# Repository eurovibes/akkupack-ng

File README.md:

<!-- SPDX-FileCopyrightText: 2024 Benedikt Spranger <b.spranger@linutronix.de> -->
<!-- SPDX-License-Identifier: CERN-OHL-S-2.0 -->

# Akkupack-NG - A AKKU-Pack gas gauge

## License rules

akkupack-ng is provided under the terms of the CERN-OHL-S license
version 2 as provided in the LICENSES/CERN-OHL-S-2.0 file.

Instead of adding license boilerplates to the individual files,
akkupack-ng uses SPDX license identifiers, which are machine parseable
and considered legaly equivalent.

The SPDX license identifier in akkupack-ng shall be added at the first
possible line in a file which can contain a comment. This is normally the
first line except for scripts. Scripts require the #!PATH_TO_INTERPRETER tag
in the first line; place the SPDX identifier into the second line.

The SPDX license identifier is added in form of a comment.

## Copyright and License

> Copyright Benedikt Spranger 2024.
> This source describes Open Hardware and is licensed under the CERNOHL-S v2.
> You may redistribute and modify this source and make products using it
> under the terms of the CERN-OHL-S v2 (https://ohwr.org/cern ohl s v2.txt ).
> This source is distributed WITHOUT ANY EXPRESS OR IMPLIED WARRANTY, INCLUDING
> OF MERCHANTABILITY, SATISFACTORY QUALITY AND FITNESS FOR A PARTICULAR PURPOSE.
> Please see the CERN-OHL-S v2 for applicable conditions.
> Source location: https://github.com/eurovibes/akkupack-ng
> As per CERN-OHL-S v2 section 4, should You produce hardware based
> on this source, You must where practicable maintain the Source Location
> visible on the external case of the akkupack-ng or other products you
> make using this source.

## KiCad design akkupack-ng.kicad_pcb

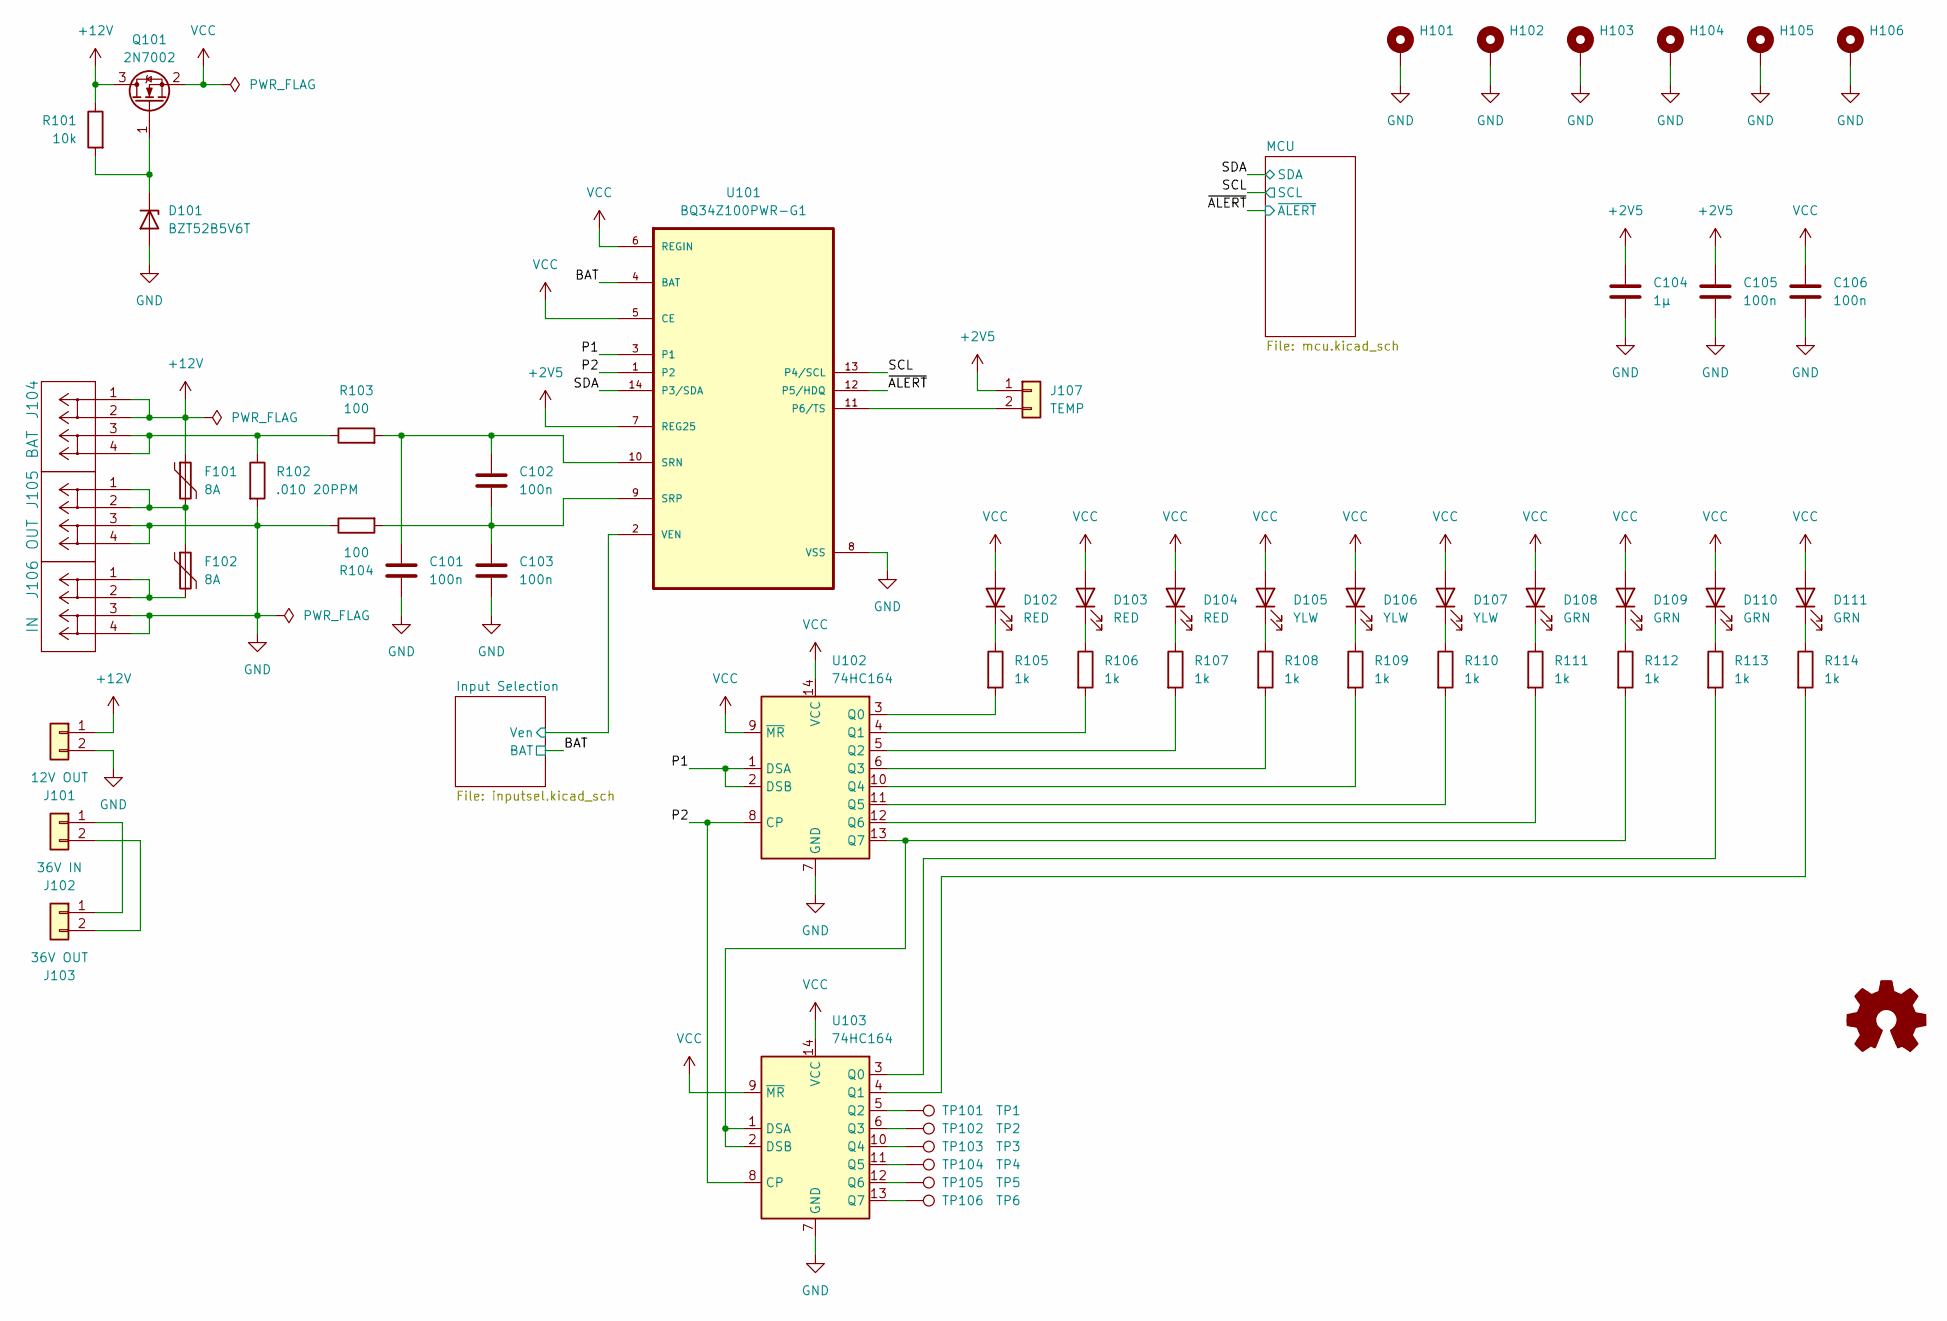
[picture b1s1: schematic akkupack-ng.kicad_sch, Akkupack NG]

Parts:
C101, C102, C103, C105, C106: 100n; C_0402_1005Metric; lcsc# C307331
C104: 1µ; C_0402_1005Metric; lcsc# C52923
D101: BZT52B5V6T; D_SOD-123F; lcsc# C22399881
D102, D103, D104: RED; LED_0603_1608Metric; lcsc# C2286
D105, D106, D107: YLW; LED_0603_1608Metric; lcsc# C965803
D108, D109, D110, D111: GRN; LED_0603_1608Metric; lcsc# C965804
F101, F102: 8A; PTR016V0800; digikey# PTR016V0800-BK-ND
H101, H102, H103, H104, H105, H106: MountingHole_3.2mm_M3_Pad
J101: 12V OUT; TerminalBlock_WAGO_236-402_1x02_P5.00mm_45Degree; digikey# 2946-236-402-ND
J102: 36V IN; TerminalBlock_WAGO_236-402_1x02_P5.00mm_45Degree; digikey# 2946-236-402-ND
J103: 36V OUT; TerminalBlock_WAGO_236-402_1x02_P5.00mm_45Degree; digikey# 2946-236-402-ND
J104: BAT; 745-302_WAGO; digikey# 2946-745-302-ND
J105: OUT; 745-302_WAGO; digikey# 2946-745-302-ND
J106: IN; 745-302_WAGO; digikey# 2946-745-302-ND
J107: TEMP; TerminalBlock_WAGO_236-402_1x02_P5.00mm_45Degree; digikey# 2946-236-402-ND
Q101: 2N7002; SOT-23; lcsc# C8545
R101: 10k; R_0402_1005Metric; lcsc# C25744
R102: .010 20PPM; R_2512_6332Metric; lcsc# C466594
R103, R104: 100; R_0402_1005Metric; lcsc# C25076
R105, R106, R107, R108, R109, R110, R111, R112, R113, R114: 1k; R_0402_1005Metric; lcsc# C11702
TP101: TP1; TestPoint_Pad_D1.0mm
TP102: TP2; TestPoint_Pad_D1.0mm
TP103: TP3; TestPoint_Pad_D1.0mm
TP104: TP4; TestPoint_Pad_D1.0mm
TP105: TP5; TestPoint_Pad_D1.0mm
TP106: TP6; TestPoint_Pad_D1.0mm
U101: BQ34Z100PWR-G1; SOP65P640X120-14N; lcsc# C91302
U102, U103: 74HC164; TSSOP-14_4.4x5mm_P0.65mm; lcsc# C406867

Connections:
+2V5: C104.1, C105.1, J107.1, U101.7 (REG25); also elsewhere on the board
+12V: F101.1, J101.1, J104.1, J104.2, Q101.3 (D), R101.1; also elsewhere on the board
/BAT: U101.4 (BAT); also elsewhere on the board
/Input Selection/Ven: U101.2 (VEN); also elsewhere on the board
/P1: U101.3 (P1), U102.1 (DSA), U102.2 (DSB)
/P2: U101.1 (P2), U102.8 (CP), U103.8 (CP)
/SCL: U101.13 (P4/SCL); also elsewhere on the board
/SDA: U101.14 (P3/SDA); also elsewhere on the board
/~ALERT: U101.12 (P5/HDQ); also elsewhere on the board
GND: C101.2, C103.2, C104.2, C105.2, C106.2, D101.2 (A), H101.1, H102.1, H103.1, H104.1, H105.1, H106.1, J101.2, J105.3, J105.4, J106.3, J106.4, R102.2, R104.1, U101.8 (VSS), U102.7 (GND), U103.7 (GND); also elsewhere on the board
unnamed: D101.1 (K), Q101.1 (G), R101.2
unnamed: D102.1 (K), R105.1
unnamed: D103.1 (K), R106.1
unnamed: D104.1 (K), R107.1
unnamed: D105.1 (K), R108.1
unnamed: D106.1 (K), R109.1
unnamed: D107.1 (K), R110.1
unnamed: D108.1 (K), R111.1
unnamed: D109.1 (K), R112.1
unnamed: D110.1 (K), R113.1
unnamed: D111.1 (K), R114.1
unnamed: F101.2, F102.1, J105.1, J105.2
unnamed: F102.2, J106.1, J106.2
unnamed: J102.1, J103.1
unnamed: J102.2, J103.2
unnamed: J104.3, J104.4, R102.1, R103.1
unnamed: J107.2, U101.11 (P6/TS)
unnamed: C101.1, C102.1, R103.2, U101.10 (SRN)
unnamed: C102.2, C103.1, R104.2, U101.9 (SRP)
unnamed: R105.2, U102.3 (Q0)
unnamed: R106.2, U102.4 (Q1)
unnamed: R107.2, U102.5 (Q2)
unnamed: R108.2, U102.6 (Q3)
unnamed: R109.2, U102.10 (Q4)
unnamed: R110.2, U102.11 (Q5)
unnamed: R111.2, U102.12 (Q6)
unnamed: R112.2, U102.13 (Q7), U103.1 (DSA), U103.2 (DSB)
unnamed: R113.2, U103.3 (Q0)
unnamed: R114.2, U103.4 (Q1)
unnamed: TP101.1, U103.5 (Q2)
unnamed: TP102.1, U103.6 (Q3)
unnamed: TP103.1, U103.10 (Q4)
unnamed: TP104.1, U103.11 (Q5)
unnamed: TP105.1, U103.12 (Q6)
unnamed: TP106.1, U103.13 (Q7)
VCC: C106.1, D102.2 (A), D103.2 (A), D104.2 (A), D105.2 (A), D106.2 (A), D107.2 (A), D108.2 (A), D109.2 (A), D110.2 (A), D111.2 (A), Q101.2 (S), U101.5 (CE), U101.6 (REGIN), U102.9 (~MR), U102.14 (VCC), U103.9 (~MR), U103.14 (VCC)

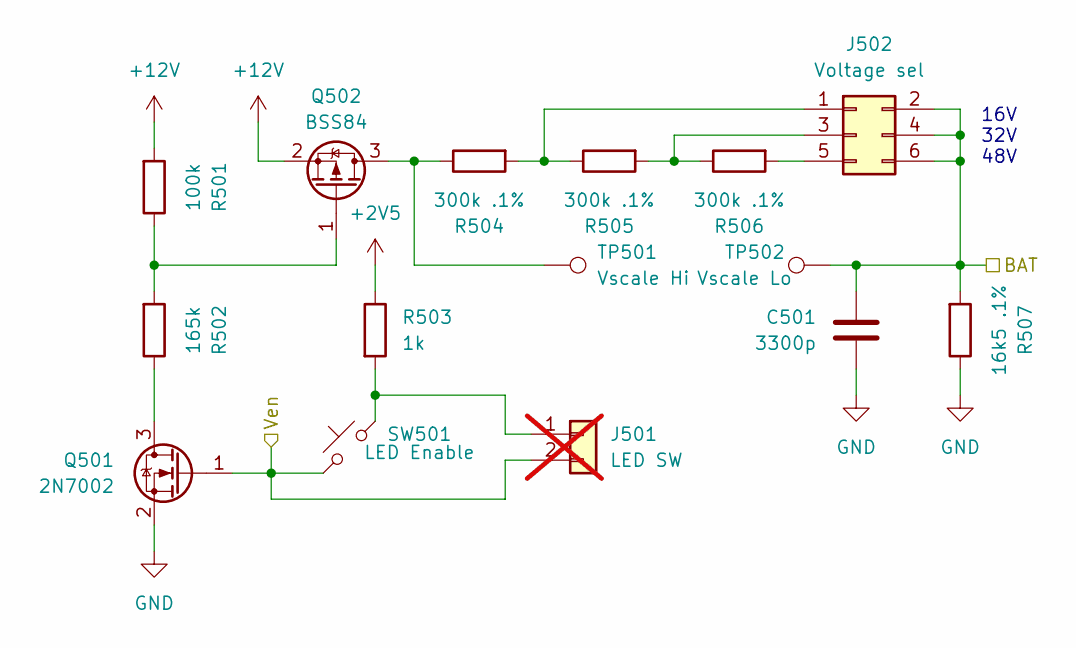
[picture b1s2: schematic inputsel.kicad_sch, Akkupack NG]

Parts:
C501: 3300p; C_1206_3216Metric; lcsc# C76663
J501: LED SW; JST_XH_B2B-XH-A_1x02_P2.50mm_Vertical; digikey# 455-B2B-XH-A-ND; not fitted
J502: Voltage sel; PinHeader_2x03_P2.54mm_Vertical
Q501: 2N7002; SOT-23; lcsc# C8545
Q502: BSS84; SOT-23; lcsc# C427395
R501: 100k; R_0402_1005Metric; lcsc# C25741
R502: 165k; R_0402_1005Metric; lcsc# C327368
R503: 1k; R_0402_1005Metric; lcsc# C11702
R504, R505, R506: 300k .1%; R_0603_1608Metric; lcsc# C335091
R507: 16k5 .1%; R_0603_1608Metric; lcsc# C861693
SW501: LED Enable; Push_SW_5x5; lcsc# C318884
TP501: Vscale Hi; TestPoint_Pad_1.5x1.5mm
TP502: Vscale Lo; TestPoint_Pad_1.5x1.5mm

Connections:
+2V5: R503.1; also elsewhere on the board
+12V: Q502.2 (S), R501.2; also elsewhere on the board
/BAT: C501.1, J502.2, J502.4, J502.6, R507.2, TP502.1; also elsewhere on the board
/Input Selection/Ven: J501.2, Q501.1 (G), SW501.1; also elsewhere on the board
GND: C501.2, Q501.2 (S), R507.1; also elsewhere on the board
unnamed: J501.1, R503.2, SW501.2
unnamed: J502.1, R504.2, R505.1
unnamed: J502.3, R505.2, R506.1
unnamed: J502.5, R506.2
unnamed: Q501.3 (D), R502.1
unnamed: Q502.3 (D), R504.1, TP501.1
unnamed: Q502.1 (G), R501.1, R502.2

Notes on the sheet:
16V 32V 48V

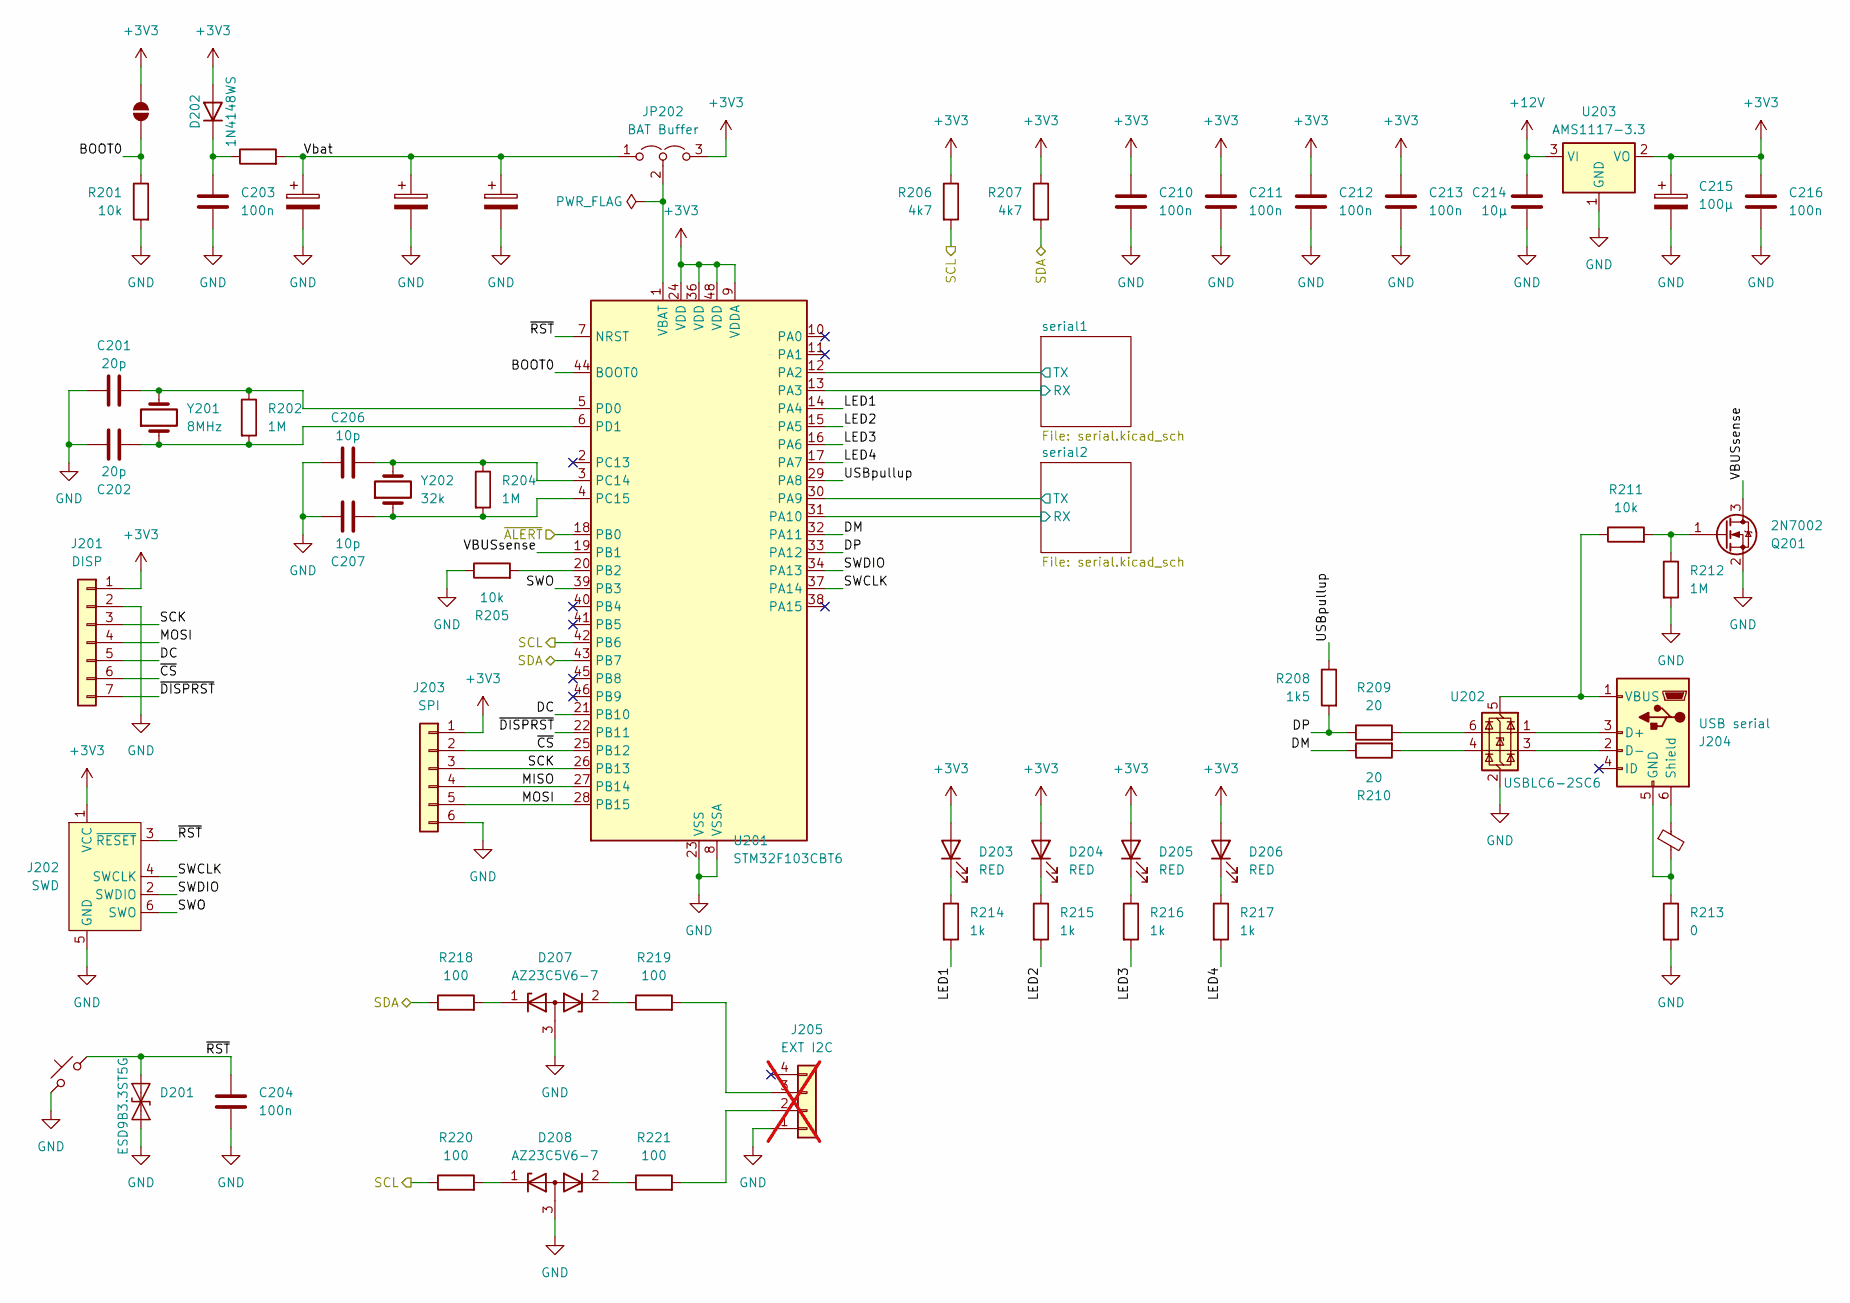
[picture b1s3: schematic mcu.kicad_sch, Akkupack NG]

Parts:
C201, C202: 20p; C_0402_1005Metric; lcsc# C1554
C203, C204, C210, C211, C212, C213, C216: 100n; C_0402_1005Metric; lcsc# C307331
C205, C208, C209: 1F; CP_Radial_D8.0mm_P3.50mm
C206, C207: 10p; C_0402_1005Metric; lcsc# C32949
C214: 10µ; C_0603_1608Metric; lcsc# C96446
C215: 100µ; CP_EIA-3528-21_Kemet-B; lcsc# C16133
D201: ESD9B3.3ST5G; D_SOD-923; lcsc# C96512
D202: 1N4148WS; D_SOD-323; lcsc# C2128
D203, D204, D205, D206: RED; LED_0603_1608Metric; lcsc# C2286
D207, D208: AZ23C5V6-7; SOT-23; lcsc# C98737
FB201: FerriteBead_Small; L_0805_2012Metric; lcsc# C1015
J201: DISP; PinSocket_1x07_P2.54mm_Vertical; digikey# 609-6552-ND
J202: SWD; Tag-Connect_TC2030-IDC-FP_2x03_P1.27mm_Vertical
J203: SPI; PinSocket_1x06_P2.54mm_Vertical; digikey# 952-1809-ND
J204: USB serial; USB_Micro-AB_Molex_47590-0001; lcsc# C136001
J205: EXT I2C; Molex_KK-254_AE-6410-04A_1x04_P2.54mm_Vertical; digikey# WM4113-ND; not fitted
JP201: BOOT0; SolderJumper-2_P1.3mm_Open_Pad1.0x1.5mm
JP202: BAT Buffer; PinHeader_1x03_P2.54mm_Vertical
Q201: 2N7002; SOT-23; lcsc# C8545
R201, R205, R211: 10k; R_0402_1005Metric; lcsc# C25744
R202, R204, R212: 1M; R_0402_1005Metric; lcsc# C26083
R203: 22; R_1206_3216Metric; lcsc# C17958
R206, R207: 4k7; R_0402_1005Metric; lcsc# C25900
R208: 1k5; R_0402_1005Metric; lcsc# C25867
R209, R210: 20; R_0603_1608Metric; lcsc# C22950
R213: 0; R_0402_1005Metric; lcsc# C17168
R214, R215, R216, R217: 1k; R_0402_1005Metric; lcsc# C11702
R218, R219, R220, R221: 100; R_0402_1005Metric; lcsc# C25076
SW201: Reset; Push_SW_5x5; lcsc# C318884
U201: STM32F103CBT6; LQFP-48_7x7mm_P0.5mm; lcsc# C8304
U202: USBLC6-2SC6; SOT-23-6; lcsc# C2827654
U203: AMS1117-3.3; SOT-223-3_TabPin2; lcsc# C6186
Y201: 8MHz; Crystal_SMD_5032-2Pin_5.0x3.2mm; lcsc# C115962
Y202: 32k; Crystal_SMD_3215-2Pin_3.2x1.5mm; lcsc# C32346

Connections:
+3V3: C210.1, C211.1, C212.1, C213.1, C215.1, C216.1, D202.2 (A), D203.2 (A), D204.2 (A), D205.2 (A), D206.2 (A), J201.1, J202.1 (VCC), J203.1, JP201.2 (B), JP202.3 (B), R206.1, R207.1, U201.9 (VDDA), U201.24 (VDD), U201.36 (VDD), U201.48 (VDD), U203.2 (VO)
+12V: C214.1, U203.3 (VI); also elsewhere on the board
/MCU/BOOT0: JP201.1 (A), R201.1, U201.44 (BOOT0)
/MCU/DC: J201.5, U201.21 (PB10)
/MCU/DM: R210.1, U201.32 (PA11)
/MCU/DP: R208.2, R209.1, U201.33 (PA12)
/MCU/LED1: R214.2, U201.14 (PA4)
/MCU/LED2: R215.2, U201.15 (PA5)
/MCU/LED3: R216.2, U201.16 (PA6)
/MCU/LED4: R217.2, U201.17 (PA7)
/MCU/MISO: J203.4, U201.27 (PB14)
/MCU/MOSI: J201.4, J203.5, U201.28 (PB15)
/MCU/SCK: J201.3, J203.3, U201.26 (PB13)
/MCU/SWCLK: J202.4 (SWCLK), U201.37 (PA14)
/MCU/SWDIO: J202.2 (SWDIO), U201.34 (PA13)
/MCU/SWO: J202.6 (SWO), U201.39 (PB3)
/MCU/USBpullup: R208.1, U201.29 (PA8)
/MCU/VBUSsense: Q201.3 (D), U201.19 (PB1)
/MCU/Vbat: C205.1, C208.1, C209.1, JP202.1 (A), R203.2
/MCU/serial1/RX: U201.13 (PA3); also elsewhere on the board
/MCU/serial1/TX: U201.12 (PA2); also elsewhere on the board
/MCU/serial2/RX: U201.31 (PA10); also elsewhere on the board
/MCU/serial2/TX: U201.30 (PA9); also elsewhere on the board
/MCU/~CS: J201.6, J203.2, U201.25 (PB12)
/MCU/~DISPRST: J201.7, U201.22 (PB11)
/MCU/~RST: C204.1, D201.2 (A2), J202.3 (~RESET), SW201.1, U201.7 (NRST)
/SCL: R206.2, R220.1, U201.42 (PB6); also elsewhere on the board
/SDA: R207.2, R218.1, U201.43 (PB7); also elsewhere on the board
/~ALERT: U201.18 (PB0); also elsewhere on the board
GND: C201.1, C202.1, C203.2, C204.2, C205.2, C206.1, C207.1, C208.2, C209.2, C210.2, C211.2, C212.2, C213.2, C214.2, C215.2, C216.2, D201.1 (A1), D207.3 (A), D208.3 (A), J201.2, J202.5 (GND), J203.6, J205.1, Q201.2 (S), R201.2, R205.1, R212.2, R213.2, SW201.2, U201.8 (VSSA), U201.23 (VSS), U201.35 (VSS), U201.47 (VSS), U202.2 (GND), U203.1 (GND); also elsewhere on the board
unnamed: C203.1, D202.1 (K), R203.1
unnamed: D203.1 (K), R214.1
unnamed: D204.1 (K), R215.1
unnamed: D205.1 (K), R216.1
unnamed: D206.1 (K), R217.1
unnamed: D207.1 (K), R218.2
unnamed: D207.2 (K), R219.1
unnamed: D208.1 (K), R220.2
unnamed: D208.2 (K), R221.1
unnamed: J204.3 (D+), U202.1 (I/O1)
unnamed: J204.2 (D-), U202.3 (I/O2)
unnamed: FB201.2, J204.5 (GND), R213.1
unnamed: FB201.1, J204.6 (Shield)
unnamed: J204.1 (VBUS), R211.1, U202.5 (VBUS)
unnamed: J205.2, R221.2
unnamed: J205.3, R219.2
unnamed: JP202.2 (C), U201.1 (VBAT)
unnamed: Q201.1 (G), R211.2, R212.1
unnamed: R209.2, U202.6 (I/O1)
unnamed: R210.2, U202.4 (I/O2)
unnamed: R205.2, U201.20 (PB2)
unnamed: C206.2, R204.1, U201.3 (PC14), Y202.2
unnamed: C207.2, R204.2, U201.4 (PC15), Y202.1
unnamed: C201.2, R202.1, U201.5 (PD0), Y201.2
unnamed: C202.2, R202.2, U201.6 (PD1), Y201.1

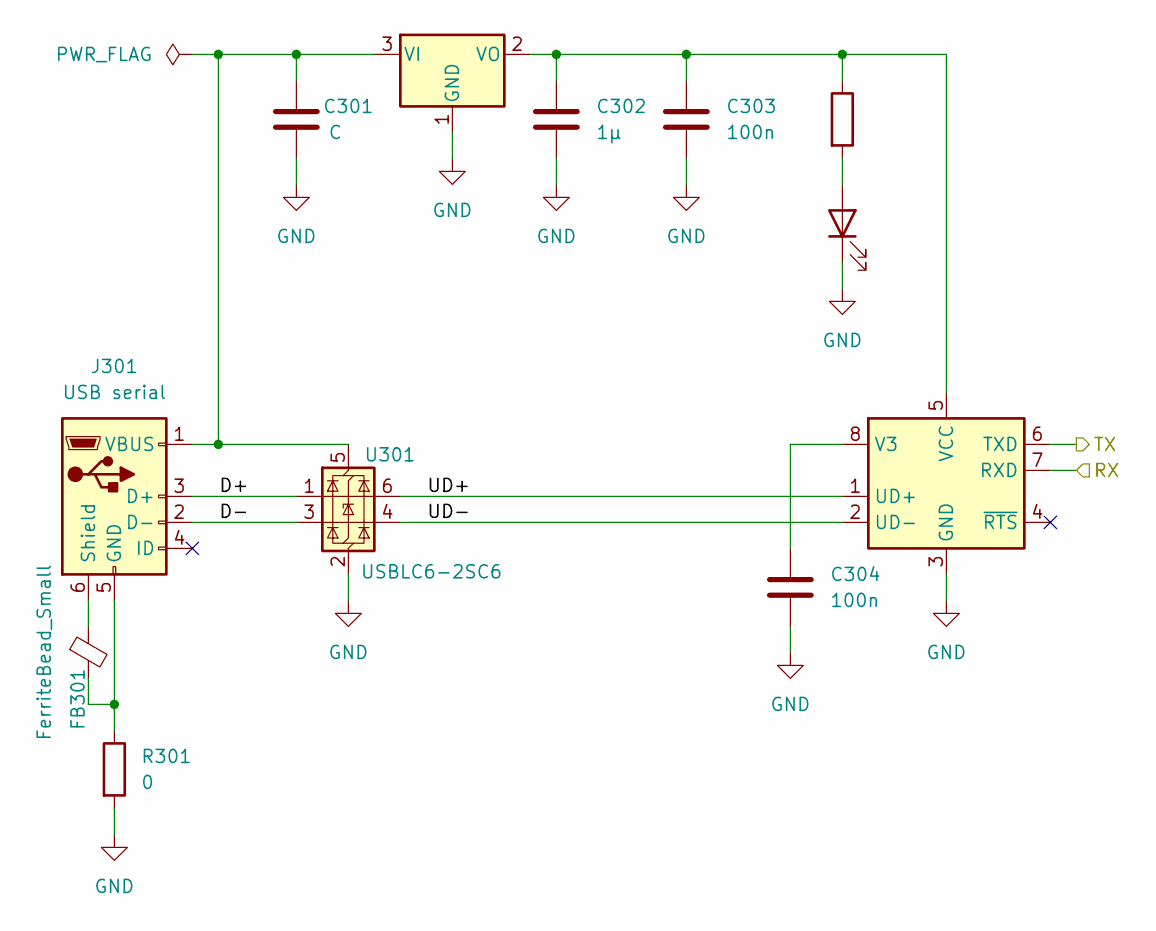
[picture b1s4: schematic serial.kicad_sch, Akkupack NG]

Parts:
C301: C; C_0805_2012Metric; lcsc# C28323
C302: 1µ; C_0402_1005Metric; lcsc# C52923
C303, C304: 100n; C_0402_1005Metric; lcsc# C307331
D301: LED; LED_0603_1608Metric; lcsc# C7371906
FB301: FerriteBead_Small; L_0805_2012Metric; lcsc# C1015
J301: USB serial; USB_Micro-AB_Molex_47590-0001; lcsc# C136001
R301: 0; R_0402_1005Metric; lcsc# C17168
R302: 1k; R_0402_1005Metric; lcsc# C11702
U301: USBLC6-2SC6; SOT-23-6; lcsc# C2827654
U302: XC6206PxxxMR; SOT-23-3; lcsc# C5446
U303: CH330N; SOIC-8_3.9x4.9mm_P1.27mm; lcsc# C2977777

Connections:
/MCU/serial1/D+: J301.3 (D+), U301.1 (I/O1)
/MCU/serial1/D-: J301.2 (D-), U301.3 (I/O2)
/MCU/serial1/RX: U303.7 (RXD); also elsewhere on the board
/MCU/serial1/TX: U303.6 (TXD); also elsewhere on the board
/MCU/serial1/UD+: U301.6 (I/O1), U303.1 (UD+)
/MCU/serial1/UD-: U301.4 (I/O2), U303.2 (UD-)
GND: C301.2, C302.2, C303.2, C304.2, D301.1 (K), R301.2, U301.2 (GND), U302.1 (GND), U303.3 (GND); also elsewhere on the board
unnamed: D301.2 (A), R302.2
unnamed: FB301.2, J301.5 (GND), R301.1
unnamed: FB301.1, J301.6 (Shield)
unnamed: C301.1, J301.1 (VBUS), U301.5 (VBUS), U302.3 (VI)
unnamed: C302.1, C303.1, R302.1, U302.2 (VO), U303.5 (VCC)
unnamed: C304.1, U303.8 (V3)

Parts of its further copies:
C401: C; C_0805_2012Metric; lcsc# C28323
C402: 1µ; C_0402_1005Metric; lcsc# C52923
C403, C404: 100n; C_0402_1005Metric; lcsc# C307331
D401: LED; LED_0603_1608Metric; lcsc# C7371906
FB401: FerriteBead_Small; L_0805_2012Metric; lcsc# C1015
J401: USB serial; USB_Micro-AB_Molex_47590-0001; lcsc# C136001
R401: 0; R_0402_1005Metric; lcsc# C17168
R402: 1k; R_0402_1005Metric; lcsc# C11702
U401: USBLC6-2SC6; SOT-23-6; lcsc# C2827654
U402: XC6206PxxxMR; SOT-23-3; lcsc# C5446
U403: CH330N; SOIC-8_3.9x4.9mm_P1.27mm; lcsc# C2977777

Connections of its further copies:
/MCU/serial2/D+: J401.3 (D+), U401.1 (I/O1)
/MCU/serial2/D-: J401.2 (D-), U401.3 (I/O2)
/MCU/serial2/RX: U403.7 (RXD); also elsewhere on the board
/MCU/serial2/TX: U403.6 (TXD); also elsewhere on the board
/MCU/serial2/UD+: U401.6 (I/O1), U403.1 (UD+)
/MCU/serial2/UD-: U401.4 (I/O2), U403.2 (UD-)
GND: C401.2, C402.2, C403.2, C404.2, D401.1 (K), R401.2, U401.2 (GND), U402.1 (GND), U403.3 (GND); also elsewhere on the board
unnamed: D401.2 (A), R402.2
unnamed: FB401.2, J401.5 (GND), R401.1
unnamed: FB401.1, J401.6 (Shield)
unnamed: C401.1, J401.1 (VBUS), U401.5 (VBUS), U402.3 (VI)
unnamed: C402.1, C403.1, R402.1, U402.2 (VO), U403.5 (VCC)
unnamed: C404.1, U403.8 (V3)

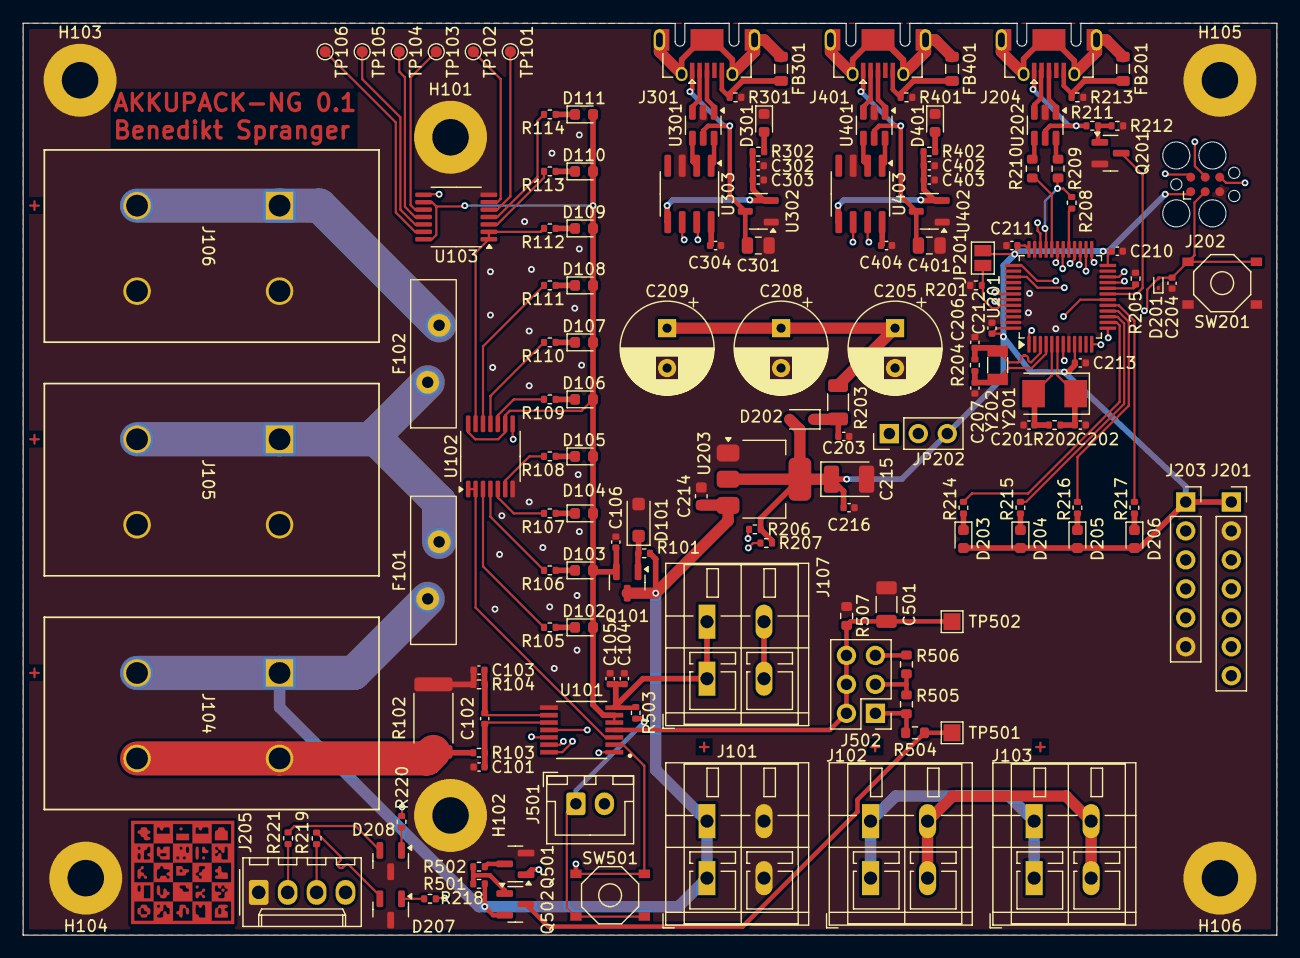
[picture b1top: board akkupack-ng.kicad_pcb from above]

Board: 4 copper layers, 109.9 x 80.0 mm, 155 parts (0 on the bottom side), 123 nets.

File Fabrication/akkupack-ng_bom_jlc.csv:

"Comment","Designator","Footprint","LCSC Part #"
"10p","C206,C207","C_0402_1005Metric","C32949"
"20p","C201,C202","C_0402_1005Metric","C1554"
"3300p","C501","C_1206_3216Metric","C76663"
"100n","C101,C102,C103,C105,C106,C203,C204,C210,C211,C212,C213,C216,C303,C304,C403,C404","C_0402_1005Metric","C307331"
"1µ","C104,C302,C402","C_0402_1005Metric","C52923"
"10µ","C214","C_0603_1608Metric","C96446"
"100µ","C215","CP_EIA-3528-21_Kemet-B","C16133"
"C","C301,C401","C_0805_2012Metric","C28323"
"1N4148WS","D202","D_SOD-323","C2128"
"AZ23C5V6-7","D207,D208","SOT-23","C98737"
"BZT52B5V6T","D101","D_SOD-123F","C2912016"
"ESD9B3.3ST5G","D201","D_SOD-923","C96512"
"GRN","D108,D109,D110,D111","LED_0603_1608Metric","C965804"
"LED","D301,D401","LED_0603_1608Metric","C7371906"
"RED","D102,D103,D104,D203,D204,D205,D206","LED_0603_1608Metric","C7371906"
"YLW","D105,D106,D107","LED_0603_1608Metric","C965803"
"FerriteBead_Small","FB201,FB301,FB401","L_0805_2012Metric","C1015"
"USB serial","J204,J301,J401","USB_Micro-AB_Molex_47590-0001","C136001"
"2N7002","Q101,Q201,Q501","SOT-23","C8545"
"BSS84","Q502","SOT-23","C427395"
"0","R213,R301,R401","R_0402_1005Metric","C17168"
".010 20PPM","R102","R_2512_6332Metric","C466594"
"20","R209,R210","R_0603_1608Metric","C22950"
"22","R203","R_1206_3216Metric","C17958"
"100","R103,R104,R218,R219,R220,R221","R_0402_1005Metric","C25076"
"1k","R105,R106,R107,R108,R109,R110,R111,R112,R113,R114,R214,R215,R216,R217,R302,R402,R503","R_0402_1005Metric","C11702"
"1k5","R208","R_0402_1005Metric","C25867"
"4k7","R206,R207","R_0402_1005Metric","C25900"
"10k","R101,R201,R205,R211","R_0402_1005Metric","C25744"
"16k5 .1%","R507","R_0603_1608Metric","C861693"
"100k","R501","R_0402_1005Metric","C25741"
"165k","R502","R_0402_1005Metric","C321332"
"300k .1%","R504,R505,R506","R_0603_1608Metric","C335091"
"1M","R202,R204,R212","R_0402_1005Metric","C25900"
"LED Enable","SW501","Push_SW_5x5","C318884"
"Reset","SW201","Push_SW_5x5","C318884"
"74HC164","U102,U103","TSSOP-14_4.4x5mm_P0.65mm","C406867"
"AMS1117-3.3","U203","SOT-223-3_TabPin2","C6186"
"BQ34Z100PWR-G1","U101","SOP65P640X120-14N","C91302"
"CH330N","U303,U403","SOIC-8_3.9x4.9mm_P1.27mm","C2977777"
"STM32F103CBT6","U201","LQFP-48_7x7mm_P0.5mm","C8304"
"USBLC6-2SC6","U202,U301,U401","SOT-23-6","C2827654"
"XC6206PxxxMR","U302,U402","SOT-23-3","C5446"
"32k","Y202","Crystal_SMD_3215-2Pin_3.2x1.5mm","C32346"
"8MHz","Y201","Crystal_SMD_5032-2Pin_5.0x3.2mm","C115962"

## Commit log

2024-05-12 Initial
2024-05-23 Add project logo
2024-05-23 Add missing 3D model
2024-05-23 Add .github automation
2024-05-23 Add README
2024-05-23 Add Blender marks
2024-05-24 Deploying to gh-pages from @ eurovibes/akkupack-ng@7ea8d4fe153b26f9fe3661b52584d7c715420190 🚀
2024-05-24 Initial gh-pages commit
2024-05-24 Deploying to gh-pages from @ eurovibes/akkupack-ng@04f2576de831c79878a0d2bb3c1a11a38931cb9c 🚀
2025-05-10 Rearange fabrication data
2025-05-10 Fix USB
2025-05-10 Deploying to gh-pages from @ eurovibes/akkupack-ng@38e2a1322359ae9fe6df4b79fb16a2588e154047 🚀
2025-05-10 Update artifact actions
    From github:
    "Starting January 30th, 2025, GitHub Actions customers will no longer be
    able to use v3 of actions/upload-artifact or actions/download-artifact."
    Update artifact actions to use v4.
2025-05-10 Rework Input selection
2025-05-10 Rework SWD connector
2025-05-12 Add BAT power disconnector
2025-05-12 Add MCU LEDs
2025-05-13 Deploying to gh-pages from @ eurovibes/akkupack-ng@028f8ceecd0bc490bd286d1ed3742376d1a2b018 🚀
2025-05-15 Deploying to gh-pages from @ eurovibes/akkupack-ng@7452a76cc23d1ee315b53fd179119e871243feb1 🚀
2025-05-15 Deploying to gh-pages from @ eurovibes/akkupack-ng@1b061a5c727c383a01161b62c78250f3fd715640 🚀
2025-05-15 Enable external I2C programming
2025-05-15 Deploying to gh-pages from @ eurovibes/akkupack-ng@d31a38aa6fd3fc88e2c7c42599cf834df72fc93f 🚀
2025-05-15 Add github action rust workflow
2025-05-15 Temp disable print schematic
2025-05-15 Update actions
2025-05-15 Add initial rust firmware implementation
2025-05-17 Available Parts
2025-05-28 Deploying to gh-pages from @ eurovibes/akkupack-ng@dcd9b4b6edc4b38bbd13cf01c1e139671d02d63c 🚀
2025-05-28 Hide obfuscating Part information from schematic
2025-05-28 Bump to version 0.2

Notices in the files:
akkupack-ng.kicad_pcb:
This work is licensed under the CERN-OHL-S v2
